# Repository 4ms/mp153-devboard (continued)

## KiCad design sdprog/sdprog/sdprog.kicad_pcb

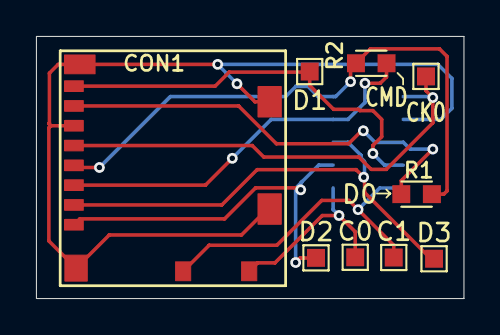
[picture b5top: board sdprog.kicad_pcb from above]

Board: 2 copper layers, 23.7 x 14.6 mm, 10 parts (1 on the bottom side), 10 nets.

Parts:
C0, C1: TestPoint; TestPoint_Pad_1.0x1.0mm
CK0: TestPoint; TestPoint_Pad_1.0x1.0mm
CON1: microSDCon_SMT_104031-0811; CardSlot_MicroSD_Molex_104031-0811
D1, D2, D3: TestPoint; TestPoint_Pad_1.0x1.0mm
J1: Socket_02x05_P1.27mm_SMT; Socket_2x05_1.27mm_SMD
R1, R2: 10k_0603; R_0603

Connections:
+3.3V: CON1.4 (VDD), J1.1, R1.1, R2.1
/CD0: C0.1, CON1.10 (SDDET1), J1.9 (GND)
/CD1: C1.1, CON1.11 (SDDET2), J1.10 (GND)
/SDMMC_CLK: CK0.1, CON1.5 (CLK), J1.2
/SDMMC_CMD: CON1.3 (CMD), J1.3, R2.2
/SDMMC_D0: CON1.7 (DAT0), J1.6, R1.2
/SDMMC_D1: CON1.8 (DAT1), D1.1, J1.8 (+12V)
/SDMMC_D2: CON1.1 (DAT2), D2.1, J1.7 (12V)
/SDMMC_D3: CON1.2 (CD/DAT3), D3.1, J1.5 (+12V)
GND: CON1.6 (VSS), CON1.9 (SHELL1), J1.4

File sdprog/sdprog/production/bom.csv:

Designator,Footprint,Quantity,Value,LCSC Part #
"C0, C1, CK0, D1, D2, D3",TestPoint_Pad_1.0x1.0mm,6,TestPoint,
CON1,CardSlot_MicroSD_Molex_104031-0811,1,microSDCon_SMT_104031-0811,C585350
J1,Socket_2x05_1.27mm_SMD,1,Socket_02x05_P1.27mm_SMT,
"R1, R2",R_0603,2,10k_0603,C98220

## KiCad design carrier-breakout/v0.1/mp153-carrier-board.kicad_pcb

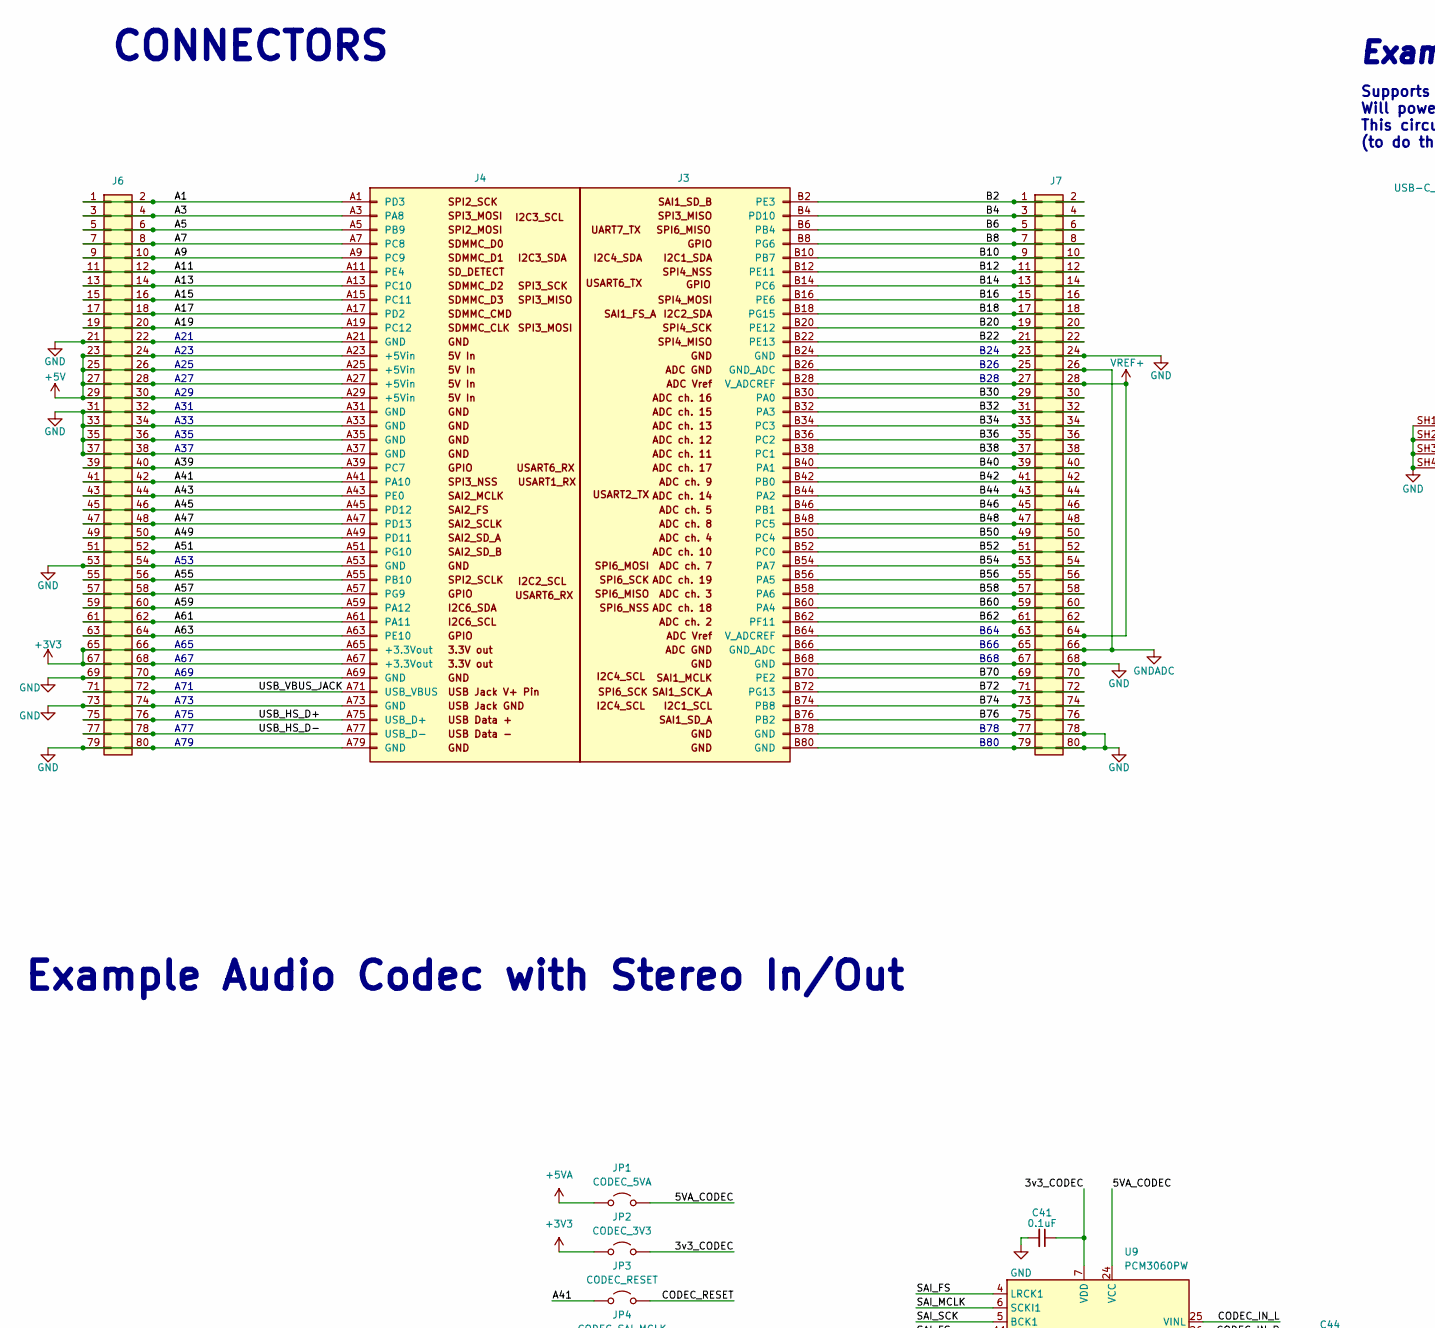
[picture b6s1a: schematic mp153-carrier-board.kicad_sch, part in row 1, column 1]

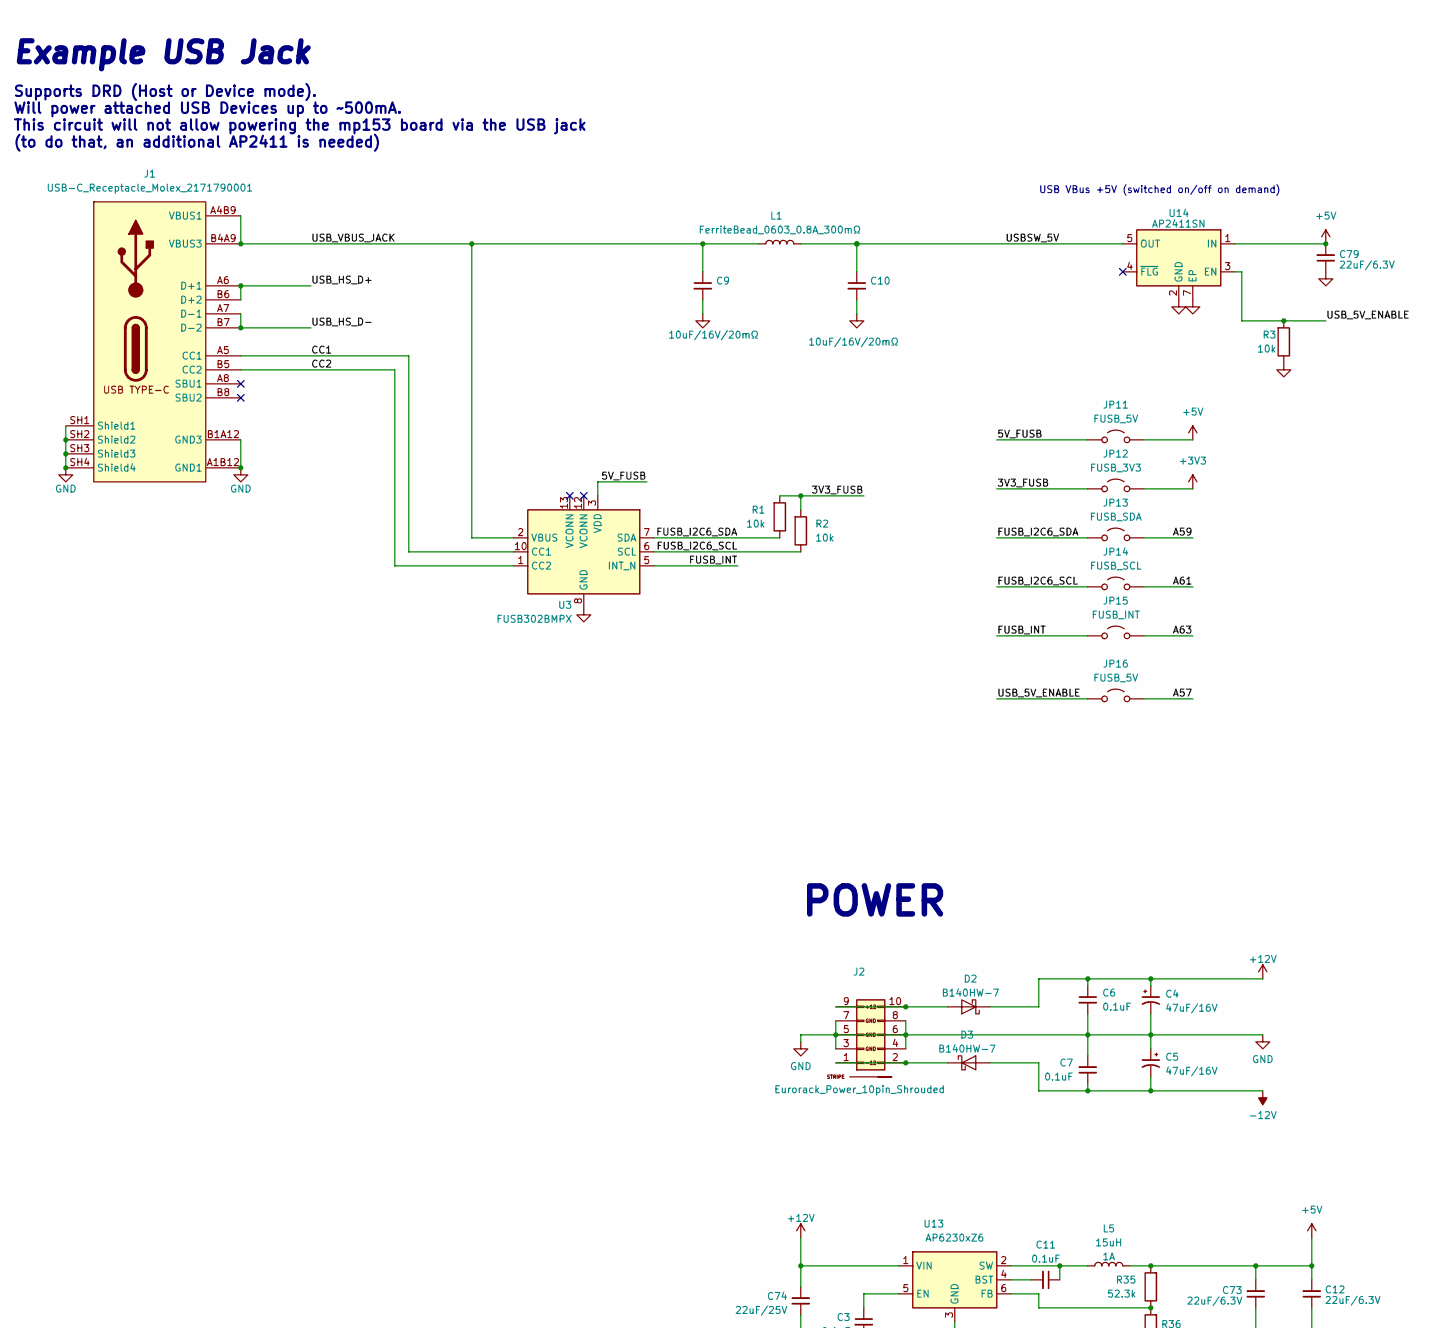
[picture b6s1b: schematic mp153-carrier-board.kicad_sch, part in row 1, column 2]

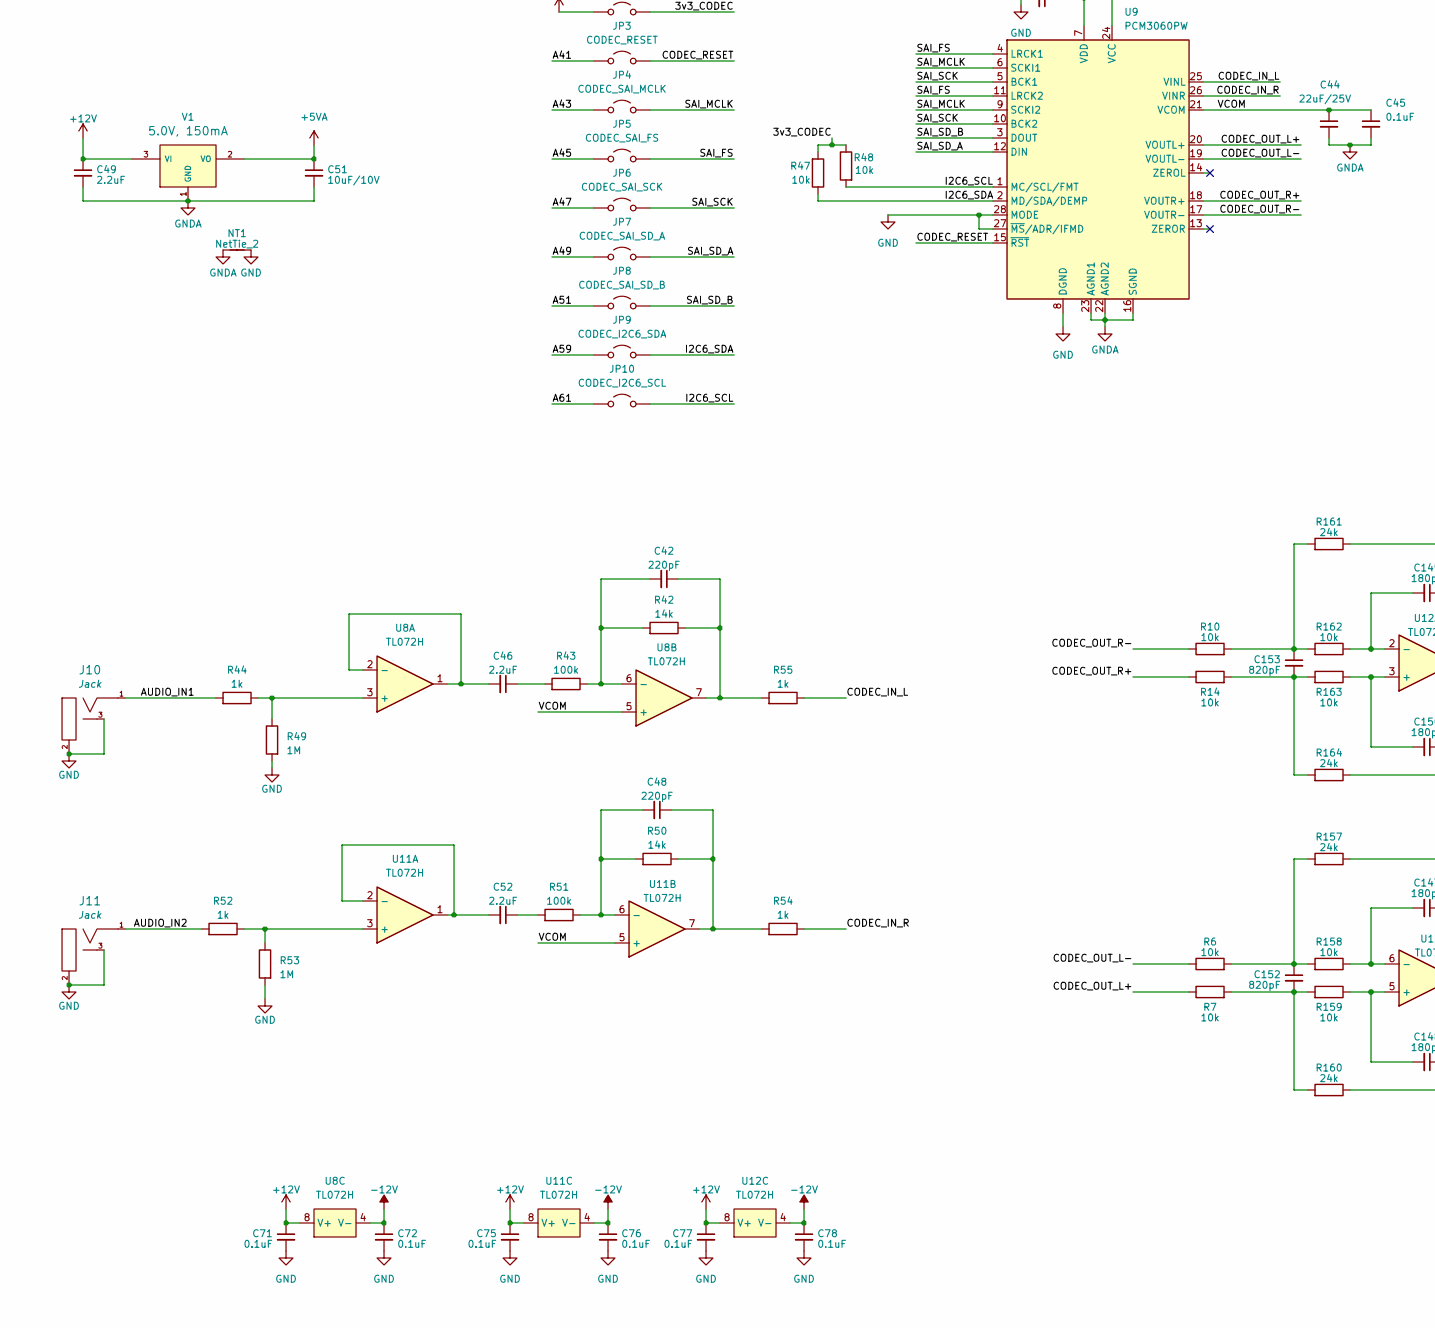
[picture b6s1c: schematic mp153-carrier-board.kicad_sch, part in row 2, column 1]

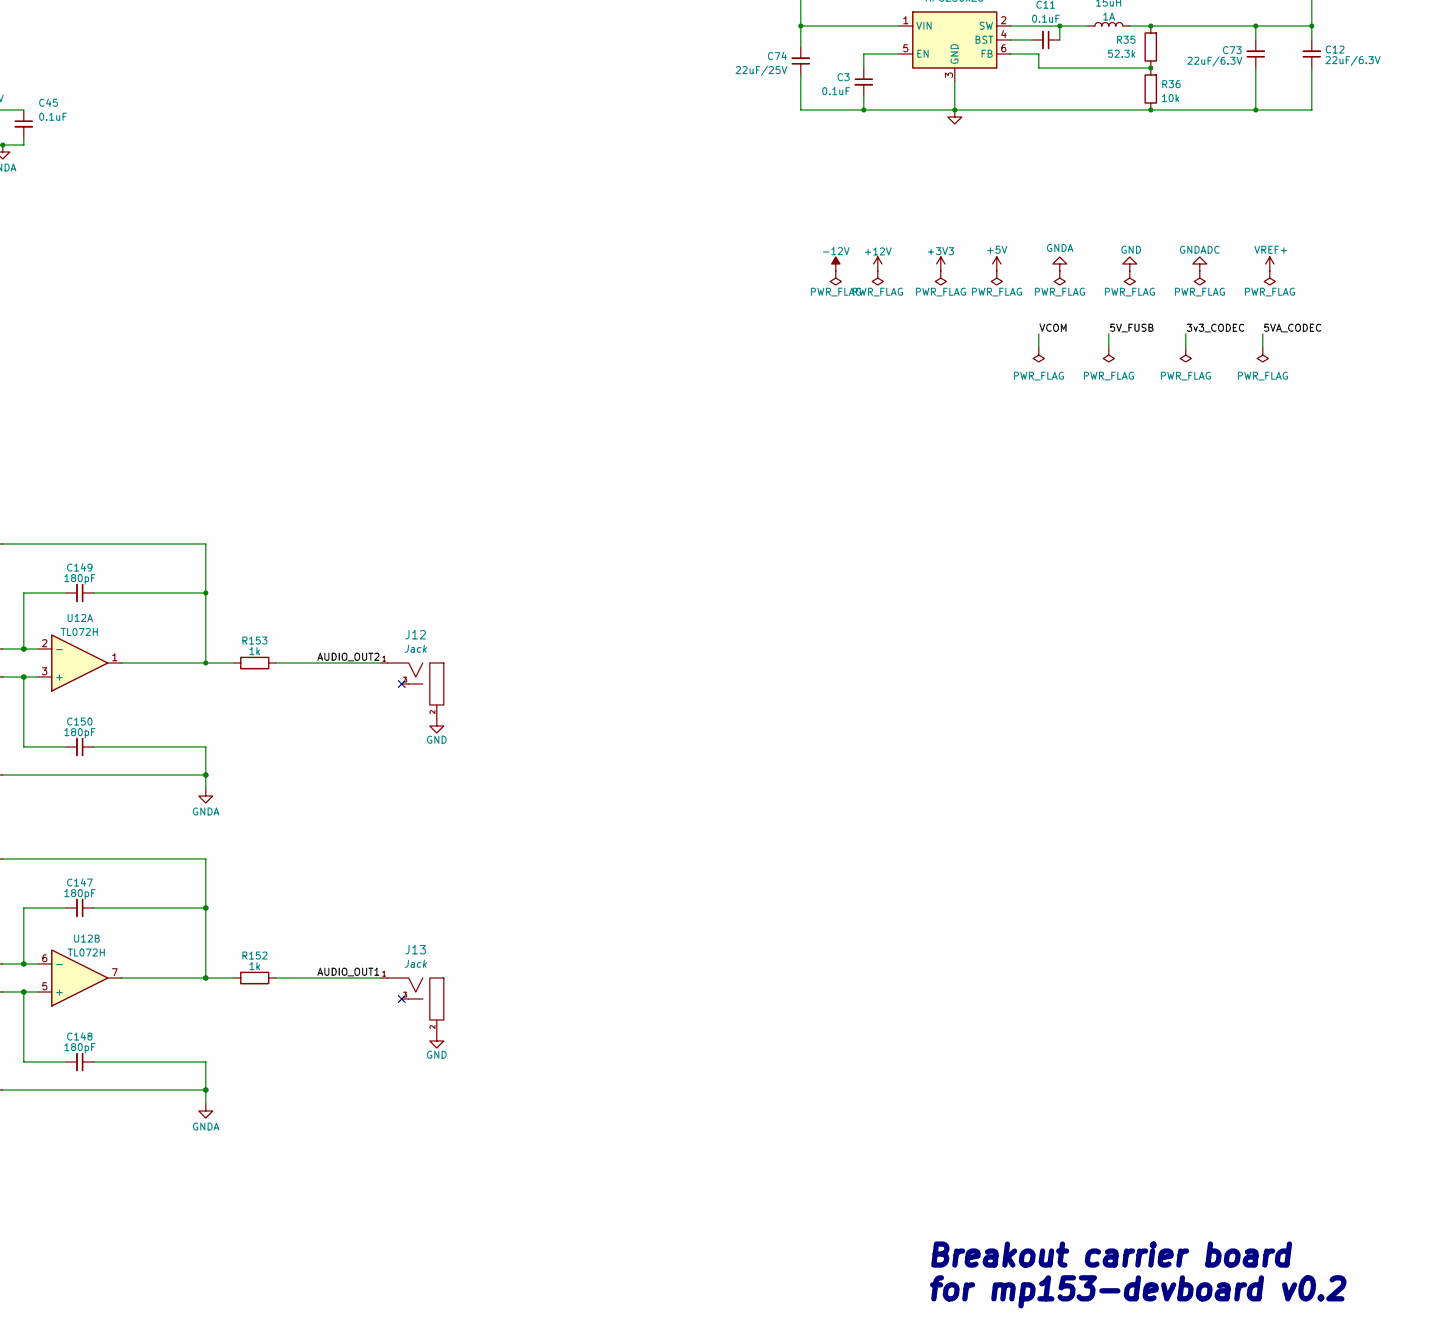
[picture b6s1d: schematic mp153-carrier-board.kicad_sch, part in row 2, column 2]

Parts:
C3, C11, C41, C45: 100nF_0402_50V; C_0402; Part Number GCM155R71C104KA55D; JLCPCB ID C1525
C4, C5: 47uF_5x5.3_16V; CP_Elec_5x5.3; Part Number VES470M1CTR-0505; JLCPCB ID C134798
C6, C7: 100nF_0603_16V; C_0603; Part Number 0603YC104KAT2A; JLCPCB ID C14663
C9, C10: 10uF_0805_16V_lowESR; C_0805; Part Number EMK212ABJ106KG-T; JLCPCB ID C190442
C12, C73, C79: 22uF_0603_6.3V; C_0603; Part Number GRM188R60J226MEA0J; JLCPCB ID C59461
C42, C48: 220pF_0603_25V; C_0603; Part Number CC0603JRNPO9BN221; JLCPCB ID C1603
C44: 22uF_0805_25V; C_0805; Part Number GRM21BR61E226ME44L; JLCPCB ID C45783
C46, C49, C52: 2.2uF_0603_25V; C_0603; Part Number GRM188R6YA225KA12D; JLCPCB ID C57895
C51: 10uF_0603_10V; C_0603; Part Number GRM188R61A106KE69D; JLCPCB ID C19702
C71, C72, C75, C76, C77, C78: 100nF_0402_50V; C_0402; Part Number GRM155R71H104KE14D; JLCPCB ID C307331
C74: 22uF_0805_25V; C_1206; Part Number TMK316BBJ226ML-T; JLCPCB ID C12891
C147, C148, C149, C150: 180pF_0402_25V; C_0402; Part Number GRM1555C2A181JE01D; JLCPCB ID C106999
C152, C153: 820pF_0402_10v; C_0402; Part Number 0402ZC821KAT2A; JLCPCB ID C565563
D2, D3: B140HW-7; D_SOD-123; Part Number B140HW-7; JLCPCB ID C134429
J1: USB-C_Receptacle_Molex_2171790001; USB_C_Receptacle_Molex_2171790001; Part Number 217179-0001; JLCPCB ID C2894899
J2: Eurorack_Power_10pin_Shrouded; Pins_2x05_2.54mm_TH_EurorackPower_Shrouded; Part Number 61201021621
J3: mp153-devboard-sockets_B; Part Number DF40HC(3.0)-80DS-0.4V(51); JLCPCB ID C2858577
J4: mp153-devboard-sockets_A; Part Number DF40HC(3.0)-80DS-0.4V(51); JLCPCB ID C2858577
J6, J7: Pins_02x40_P2.54mm_TH; Pins_2x40_P2.54mm_TH
J10, J11, J12, J13: 3.5mm_Mono_Switched_sm; EighthInch_PJ398SM; Part Number WQP-WQP518MA
JP1, JP2, JP3, JP4, JP5, JP6, JP7, JP8, JP9, JP10, JP11, JP12, JP13, JP14, JP15, JP16: SolderJumper_2_Open; JUMPER_SMD_1x2_tiny
L1: FerriteBead_0603_0.8A_300mΩ; R_0603; Part Number MPZ1608S102ATA00; JLCPCB ID C76814
L5: 15uH_1A_5040; COIL_5040; Part Number SRN5040TA-150M; JLCPCB ID C222950
NT1: NetTie_2; NetTie-2_SMD_Pad0.5mm
R1, R2, R3, R6, R7, R10, R14, R36, R47, R48, R158, R159, R162, R163: 10k_0402; R_0402; Part Number RC0402FR-0710KL; JLCPCB ID C60490
R35: 52.3k_0402; R_0402; Part Number RC0402FR-0752K3L; JLCPCB ID C276275
R42, R50: 14k_0402; R_0402; Part Number RC0402FR-0714KL; JLCPCB ID C327372
R43, R51: 100k_0402; R_0402; Part Number RC0402FR-07100KL; JLCPCB ID C60491
R44, R52, R54, R55, R152, R153: 1k_0402; R_0402; Part Number RC0402FR-071KL; JLCPCB ID C106235
R49, R53: 1M_0402; R_0402; Part Number RC0402FR-071ML; JLCPCB ID C138033
R157, R160, R161, R164: 24k_0402; R_0402; Part Number RC0402FR-0724KL; JLCPCB ID C138026
U3: FUSB302BMPX; WQFN-14-1EP_2.5x2.5mm_P0.5mm_EP1.45x1.45mm; Part Number FUSB302BMPX; JLCPCB ID C132291
U8, U11, U12: TL072H; TSSOP-8_4.4x3mm_Pitch0.65mm; Part Number TL072HIPWR; JLCPCB ID C4370341
U9: PCM3060PW; TSSOP-28_4.4x9.7mm_P0.65mm; Part Number PCM3060PW; JLCPCB ID C2651841
U13: AP6230xZ6; SOT-563; Part Number AP62301Z6; JLCPCB ID C1880992
U14: AP2411SN; DFN-6-1EP_2x2mm_P0.65mm_EP1x1.6mm; Part Number AP2411SN-7; JLCPCB ID C2149815
V1: AP2120N-5.0TRG1; SOT23-3_PO132; Part Number AP2120N-5.0TRG1; JLCPCB ID C50754

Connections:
+3V3: J4.A65 (+3.3Vout), J4.A67 (+3.3Vout), J6.65, J6.66, J6.67, J6.68, JP2.1 (A), JP12.2 (B)
+5V: C12.2, C73.2, C79.2, J4.A23 (+5Vin), J4.A25 (+5Vin), J4.A27 (+5Vin), J4.A29 (+5Vin), J6.23, J6.24, J6.25, J6.26, J6.27, J6.28, J6.29, J6.30, JP11.2 (B), L5.2, R35.2, U14.1 (IN)
+5VA: C51.1, JP1.1 (A), V1.2 (VO)
+12V: C4.1, C6.1, C49.1, C71.1, C74.2, C75.1, C77.1, D2.1 (K), U8.8 (V+), U11.8 (V+), U12.8 (V+), U13.1 (VIN), V1.3 (VI)
-12V: C5.2, C7.1, C72.1, C76.1, C78.1, D3.2 (A), U8.4 (V-), U11.4 (V-), U12.4 (V-)
/3V3_FUSB: JP12.1 (A), R1.2, R2.2
/3v3_CODEC: C41.1, JP2.2 (B), R47.2, R48.1, U9.7 (VDD)
/5VA_CODEC: JP1.2 (B), U9.24 (VCC)
/5V_FUSB: JP11.1 (A), U3.3 (VDD), U3.4 (VDD)
/A1: J4.A1 (PD3), J6.1, J6.2
/A3: J4.A3 (PA8), J6.3, J6.4
/A5: J4.A5 (PB9), J6.5, J6.6
/A7: J4.A7 (PC8), J6.7, J6.8
/A9: J4.A9 (PC9), J6.9, J6.10
/A11: J4.A11 (PE4), J6.11, J6.12
/A13: J4.A13 (PC10), J6.13, J6.14
/A15: J4.A15 (PC11), J6.15, J6.16
/A17: J4.A17 (PD2), J6.17, J6.18
/A19: J4.A19 (PC12), J6.19, J6.20
/A39: J4.A39 (PC7), J6.39, J6.40
/A41: J4.A41 (PA10), J6.41, J6.42, JP3.1 (A)
/A43: J4.A43 (PE0), J6.43, J6.44, JP4.1 (A)
/A45: J4.A45 (PD12), J6.45, J6.46, JP5.1 (A)
/A47: J4.A47 (PD13), J6.47, J6.48, JP6.1 (A)
/A49: J4.A49 (PD11), J6.49, J6.50, JP7.1 (A)
/A51: J4.A51 (PG10), J6.51, J6.52, JP8.1 (A)
/A55: J4.A55 (PB10), J6.55, J6.56
/A57: J4.A57 (PG9), J6.57, J6.58, JP16.2 (B)
/A59: J4.A59 (PA12), J6.59, J6.60, JP9.1 (A), JP13.2 (B)
/A61: J4.A61 (PA11), J6.61, J6.62, JP10.1 (A), JP14.2 (B)
/A63: J4.A63 (PE10), J6.63, J6.64, JP15.2 (B)
/AUDIO_IN1: J10.1 (SIG), R44.2
/AUDIO_IN2: J11.1 (SIG), R52.2
/AUDIO_OUT1: J13.1 (SIG), R152.1
/AUDIO_OUT2: J12.1 (SIG), R153.1
/B2: J3.B2 (PE3), J7.1, J7.2
/B4: J3.B4 (PD10), J7.3, J7.4
/B6: J3.B6 (PB4), J7.5, J7.6
/B8: J3.B8 (PG6), J7.7, J7.8
/B10: J3.B10 (PB7), J7.9, J7.10
/B12: J3.B12 (PE11), J7.11, J7.12
/B14: J3.B14 (PC6), J7.13, J7.14
/B16: J3.B16 (PE6), J7.15, J7.16
/B18: J3.B18 (PG15), J7.17, J7.18
/B20: J3.B20 (PE12), J7.19, J7.20
/B22: J3.B22 (PE13), J7.21, J7.22
/B30: J3.B30 (PA0), J7.29, J7.30
/B32: J3.B32 (PA3), J7.31, J7.32
/B34: J3.B34 (PC3), J7.33, J7.34
/B36: J3.B36 (PC2), J7.35, J7.36
/B38: J3.B38 (PC1), J7.37, J7.38
/B40: J3.B40 (PA1), J7.39, J7.40
/B42: J3.B42 (PB0), J7.41, J7.42
/B44: J3.B44 (PA2), J7.43, J7.44
/B46: J3.B46 (PB1), J7.45, J7.46
/B48: J3.B48 (PC5), J7.47, J7.48
/B50: J3.B50 (PC4), J7.49, J7.50
/B52: J3.B52 (PC0), J7.51, J7.52
/B54: J3.B54 (PA7), J7.53, J7.54
/B56: J3.B56 (PA5), J7.55, J7.56
/B58: J3.B58 (PA6), J7.57, J7.58
/B60: J3.B60 (PA4), J7.59, J7.60
/B62: J3.B62 (PF11), J7.61, J7.62
/B70: J3.B70 (PE2), J7.69, J7.70
/B72: J3.B72 (PG13), J7.71, J7.72
/B74: J3.B74 (PB8), J7.73, J7.74
/B76: J3.B76 (PB2), J7.75, J7.76
/CC1: J1.A5 (CC1), U3.10 (CC1), U3.11 (CC1)
/CC2: J1.B5 (CC2), U3.1 (CC2), U3.14 (CC2)
/CODEC_IN_L: R55.1, U9.25 (VINL)
/CODEC_IN_R: R54.1, U9.26 (VINR)
/CODEC_OUT_L+: R7.1, U9.20 (VOUTL+)
/CODEC_OUT_L-: R6.1, U9.19 (VOUTL-)
/CODEC_OUT_R+: R14.1, U9.18 (VOUTR+)
/CODEC_OUT_R-: R10.1, U9.17 (VOUTR-)
/CODEC_RESET: JP3.2 (B), U9.15 (~RST)
/FUSB_I2C6_SCL: JP14.1 (A), R2.1, U3.6 (SCL)
/FUSB_I2C6_SDA: JP13.1 (A), R1.1, U3.7 (SDA)
/FUSB_INT: JP15.1 (A), U3.5 (INT_N)
/I2C6_SCL: JP10.2 (B), R48.2, U9.1 (MC/SCL/FMT)
/I2C6_SDA: JP9.2 (B), R47.1, U9.2 (MD/SDA/DEMP)
/SAI_FS: JP5.2 (B), U9.4 (LRCK1), U9.11 (LRCK2)
/SAI_MCLK: JP4.2 (B), U9.6 (SCKI1), U9.9 (SCKI2)
/SAI_SCK: JP6.2 (B), U9.5 (BCK1), U9.10 (BCK2)
/SAI_SD_A: JP7.2 (B), U9.12 (DIN)
/SAI_SD_B: JP8.2 (B), U9.3 (DOUT)
/USBSW_5V: C10.1, L1.1, U14.5 (OUT)
/USB_5V_ENABLE: JP16.1 (A), R3.2, U14.3 (EN)
/USB_HS_D+: J1.A6 (D+1), J1.B6 (D+2), J4.A75 (USB_D+), J6.75, J6.76
/USB_HS_D-: J1.A7 (D-1), J1.B7 (D-2), J4.A77 (USB_D-), J6.77, J6.78
/USB_VBUS_JACK: C9.1, J1.A4B9 (VBUS1), J1.B4A9 (VBUS3), J4.A71 (USB_VBUS), J6.71, J6.72, L1.2, U3.2 (VBUS)
/VCOM: C44.1, C45.1, U8.5 (+), U9.21 (VCOM), U11.5 (+)
GND: C3.2, C4.2, C5.1, C6.2, C7.2, C9.2, C10.2, C12.1, C41.2, C71.2, C72.2, C73.1, C74.1, C75.2, C76.2, C77.2, C78.2, C79.1, J1.A1B12 (GND1), J1.B1A12 (GND3), J1.SH1 (Shield1), J1.SH2 (Shield2), J1.SH3 (Shield3), J1.SH4 (Shield4), J2.3 (GND), J2.4 (GND), J2.5 (GND), J2.6 (GND), J2.7 (GND), J2.8 (GND), J3.B24 (GND), J3.B68 (GND), J3.B78 (GND), J3.B80 (GND), J4.A21 (GND), J4.A31 (GND), J4.A33 (GND), J4.A35 (GND), J4.A37 (GND), J4.A53 (GND), J4.A69 (GND), J4.A73 (GND), J4.A79 (GND), J6.21, J6.22, J6.31, J6.32, J6.33, J6.34, J6.35, J6.36, J6.37, J6.38, J6.53, J6.54, J6.69, J6.70, J6.73, J6.74, J6.79, J6.80, J7.23, J7.24, J7.67, J7.68, J7.77, J7.78, J7.79, J7.80, J10.2 (SHEILD), J10.3 (SW), J11.2 (SHEILD), J11.3 (SW), J12.2 (SHEILD), J13.2 (SHEILD), NT1.2, R3.1, R36.1, R49.2, R53.2, U3.8 (GND), U3.9 (GND), U3.15 (GND), U9.8 (DGND), U9.27 (~MS/ADR/IFMD), U9.28 (MODE), U13.3 (GND), U14.2 (GND), U14.7 (EP)
GNDA: C44.2, C45.2, C49.2, C51.2, C148.1, C150.1, NT1.1, R160.1, R164.1, U9.16 (SGND), U9.22 (AGND2), U9.23 (AGND1), V1.1 (GND)
GNDADC: J3.B26 (GND_ADC), J3.B66 (GND_ADC), J7.25, J7.26, J7.65, J7.66
unnamed: C42.1, R42.1, R55.2, U8.7
unnamed: C46.1, R43.2
unnamed: C48.1, R50.1, R54.2, U11.7
unnamed: C52.1, R51.2
unnamed: C147.1, R152.2, R157.1, U12.7
unnamed: C149.1, R153.2, R161.1, U12.1
unnamed: C152.1, R6.2, R157.2, R158.2
unnamed: C152.2, R7.2, R159.2, R160.2
unnamed: C153.1, R10.2, R161.2, R162.2
unnamed: C153.2, R14.2, R163.2, R164.2
unnamed: D2.2 (A), J2.9 (+12V), J2.10 (+12V)
unnamed: D3.1 (K), J2.1 (-12V), J2.2 (-12V)
unnamed: R44.1, R49.1, U8.3 (+)
unnamed: C46.2, U8.1, U8.2 (-)
unnamed: C42.2, R42.2, R43.1, U8.6 (-)
unnamed: R52.1, R53.1, U11.3 (+)
unnamed: C52.2, U11.1, U11.2 (-)
unnamed: C48.2, R50.2, R51.1, U11.6 (-)
unnamed: C150.2, R163.1, U12.3 (+)
unnamed: C149.2, R162.1, U12.2 (-)
unnamed: C148.2, R159.1, U12.5 (+)
unnamed: C147.2, R158.1, U12.6 (-)
unnamed: C11.2, U13.4 (BST)
unnamed: C3.1, U13.5 (EN)
unnamed: R35.1, R36.2, U13.6 (FB)
unnamed: C11.1, L5.1, U13.2 (SW)
VREF+: J3.B28 (V_ADCREF), J3.B64 (V_ADCREF), J7.27, J7.28, J7.63, J7.64

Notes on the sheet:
A73
A37
A33
A77
POWER
B80
A65
B64
A25
A71
A69
B28
B24
CONNECTORS
B26
B68
Supports DRD (Host or Device mode). Will power attached USB Devices up to ~500mA. This circuit will not allow powering the mp153 board via the USB jack (to do that, an additional AP2411 is needed)
A79
A75
Example USB Jack
A67
Example Audio Codec with Stereo In/Out
A31
A29
A21
Breakout carrier board for mp153-devboard v0.2
B78
B66
A35
USB VBus +5V (switched on/off on demand)
A53
A23
A27

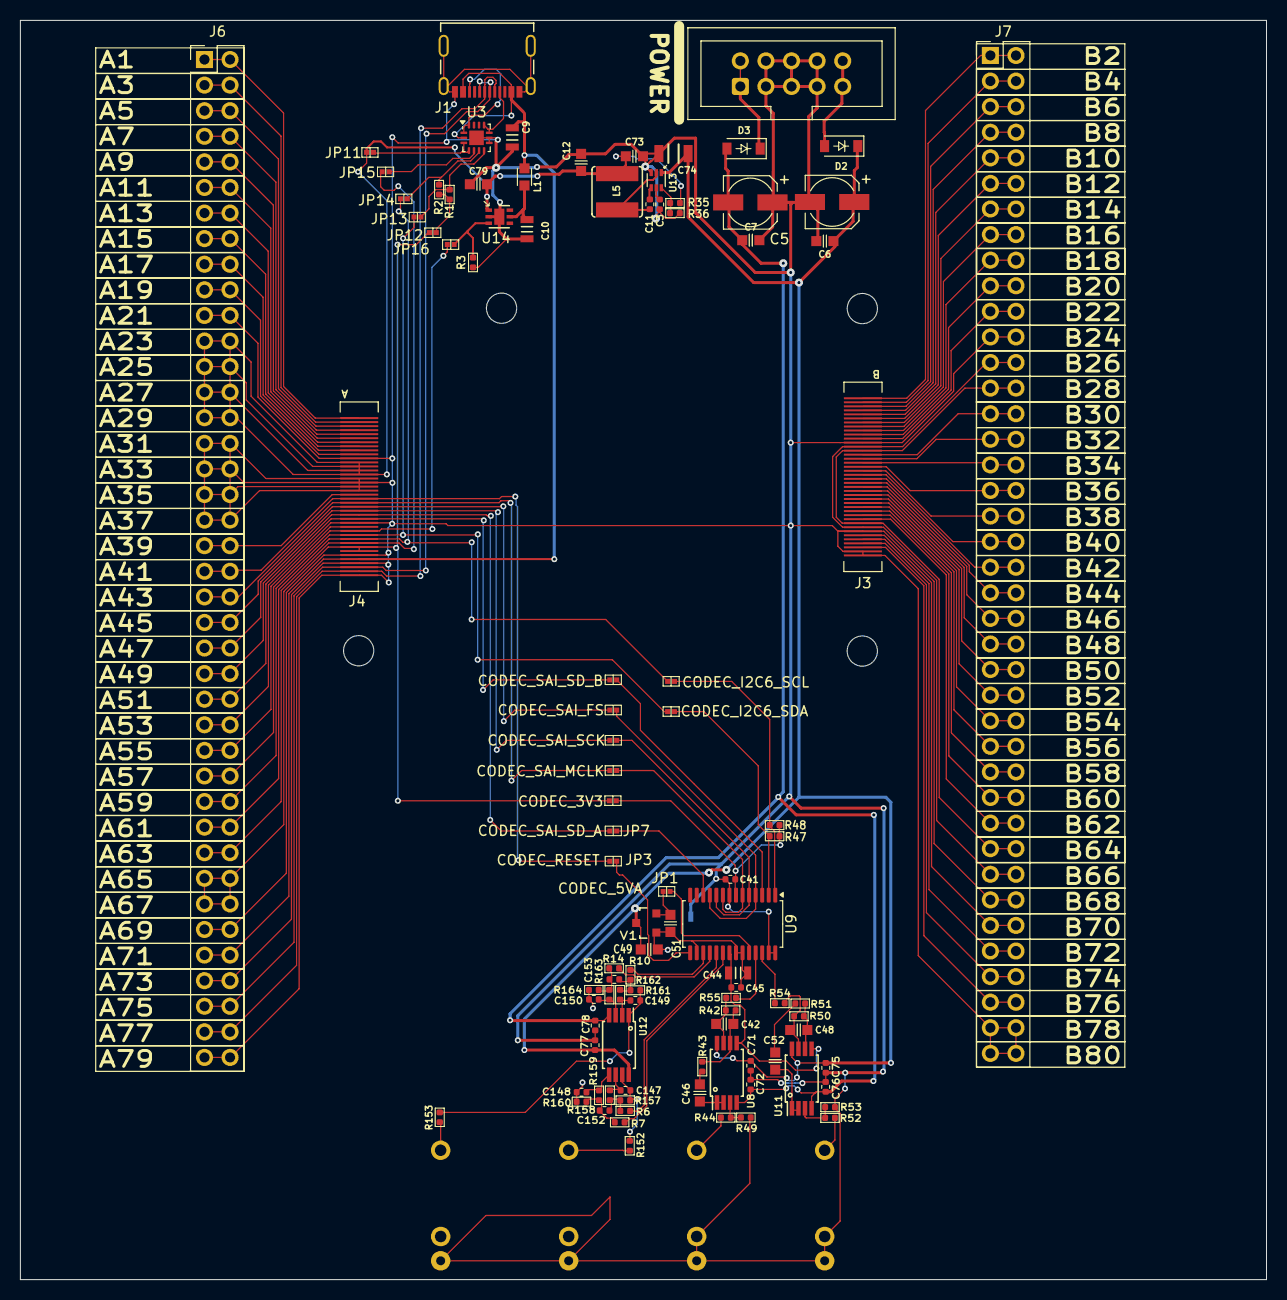
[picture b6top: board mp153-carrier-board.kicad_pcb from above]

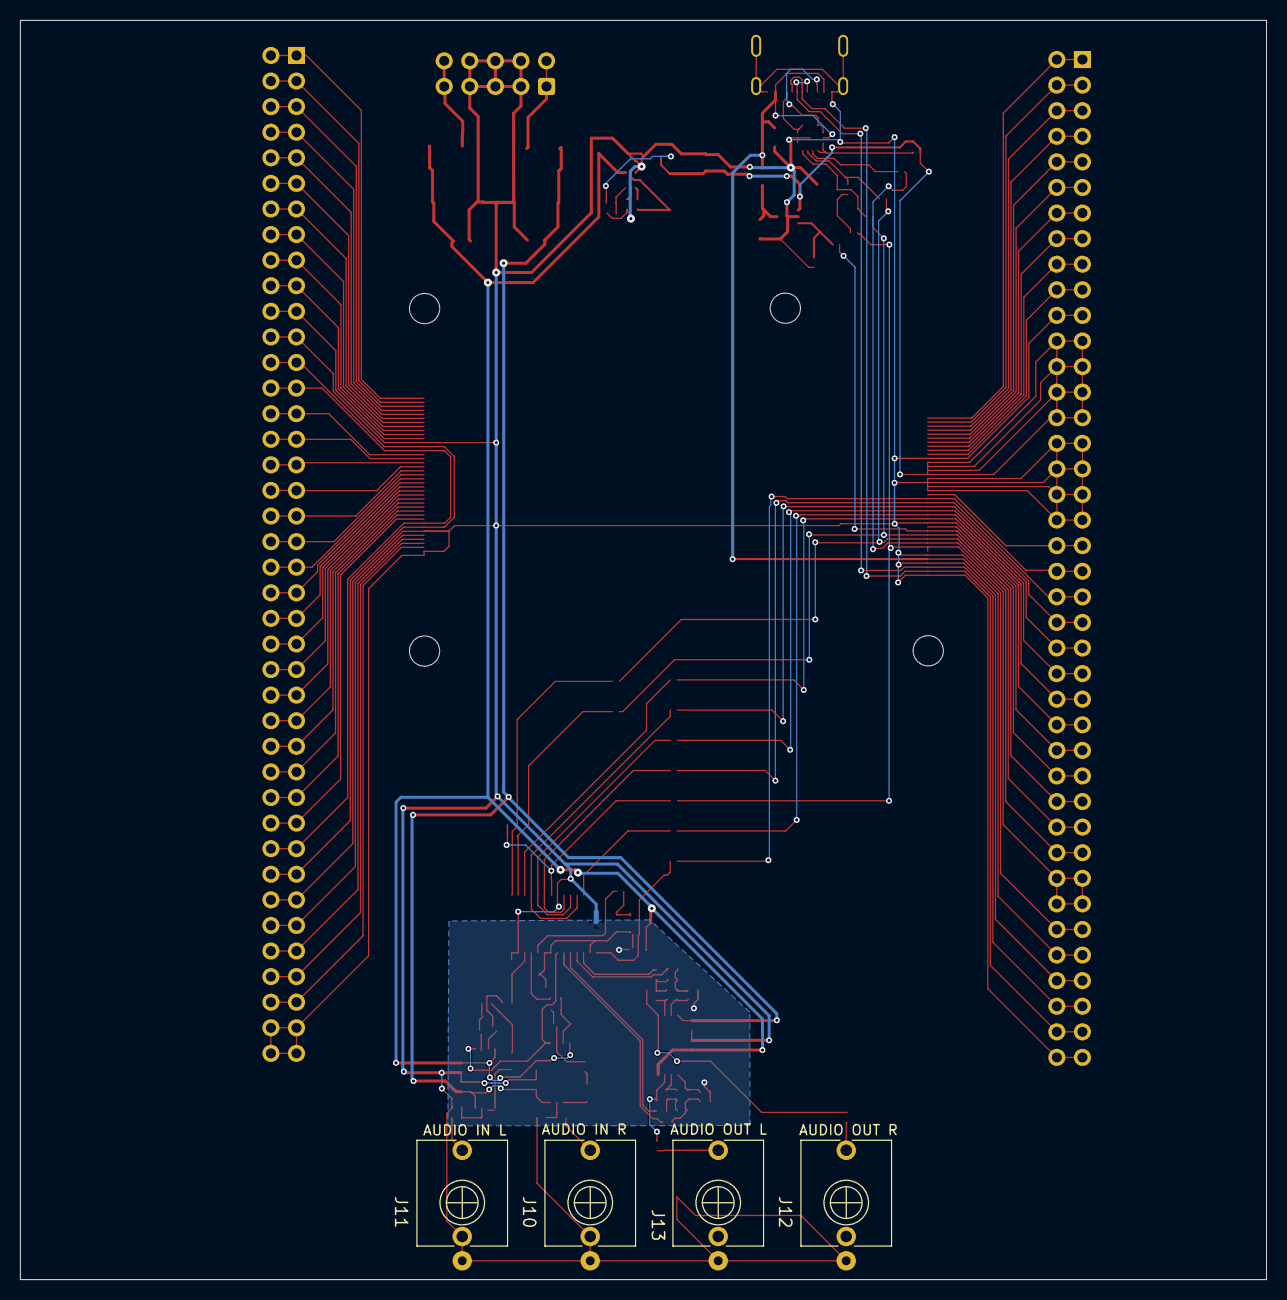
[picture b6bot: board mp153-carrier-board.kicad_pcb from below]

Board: 2 copper layers, 123.7 x 125.0 mm, 103 parts (5 on the bottom side), 122 nets.

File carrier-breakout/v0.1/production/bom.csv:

Designator,Footprint,Quantity,Value,LCSC Part #
"C10, C9",C_0805,2,10uF_0805_16V_lowESR,C190442
"C11, C3, C41, C45",C_0402,4,100nF_0402_50V,C1525
"C12, C73, C79",C_0603,3,22uF_0603_6.3V,C59461
"C147, C148, C149, C150",C_0402,4,180pF_0402_25V,C106999
"C152, C153",C_0402,2,820pF_0402_10v,C565563
"C4, C5",CP_Elec_5x5.3,2,47uF_5x5.3_16V,C134798
"C42, C48",C_0603,2,220pF_0603_25V,C1603
C44,C_0805,1,22uF_0805_25V,C45783
"C46, C49, C52",C_0603,3,2.2uF_0603_25V,C57895
C51,C_0603,1,10uF_0603_10V,C19702
"C6, C7",C_0603,2,100nF_0603_16V,C14663
"C71, C72, C75, C76, C77, C78",C_0402,6,100nF_0402_50V,C307331
C74,C_1206,1,22uF_0805_25V,C12891
"D2, D3",D_SOD-123,2,B140HW-7,C134429
J1,USB_C_Receptacle_Molex_2171790001,1,USB-C_Receptacle_Molex_2171790001,C2894899
"J10, J11, J12, J13",EighthInch_PJ398SM,4,3.5mm_Mono_Switched_sm,
J2,Pins_2x05_2.54mm_TH_EurorackPower_Shrouded,1,Eurorack_Power_10pin_Shrouded,
J3,mp153-devboard-sockets_B,1,~,C2858577
J4,mp153-devboard-sockets_A,1,~,C2858577
"J6, J7",Pins_2x40_P2.54mm_TH,2,Pins_02x40_P2.54mm_TH,
"JP1, JP10, JP11, JP12, JP13, JP14, JP15, JP16, JP2, JP3, JP4, JP5, JP6, JP7, JP8, JP9",JUMPER_SMD_1x2_tiny,16,SolderJumper_2_Open,
L1,R_0603,1,FerriteBead_0603_0.8A_300mΩ,C76814
L5,COIL_5040,1,15uH_1A_5040,C222950
"R1, R10, R14, R158, R159, R162, R163, R2, R3, R36, R47, R48, R6, R7",R_0402,14,10k_0402,C60490
"R152, R153, R44, R52, R54, R55",R_0402,6,1k_0402,C106235
"R157, R160, R161, R164",R_0402,4,24k_0402,C138026
R35,R_0402,1,52.3k_0402,C276275
"R42, R50",R_0402,2,14k_0402,C327372
"R43, R51",R_0402,2,100k_0402,C60491
"R49, R53",R_0402,2,1M_0402,C138033
"U11, U12, U8",TSSOP-8_4.4x3mm_Pitch0.65mm,3,TL072H,C4370341
U13,SOT-563,1,AP6230xZ6,C1880992
U14,DFN-6-1EP_2x2mm_P0.65mm_EP1x1.6mm,1,AP2411SN,C2149815
U3,WQFN-14-1EP_2.5x2.5mm_P0.5mm_EP1.45x1.45mm,1,FUSB302BMPX,C132291
U9,TSSOP-28_4.4x9.7mm_P0.65mm,1,PCM3060PW,C2651841
V1,SOT23-3_PO132,1,AP2120N-5.0TRG1,C50754

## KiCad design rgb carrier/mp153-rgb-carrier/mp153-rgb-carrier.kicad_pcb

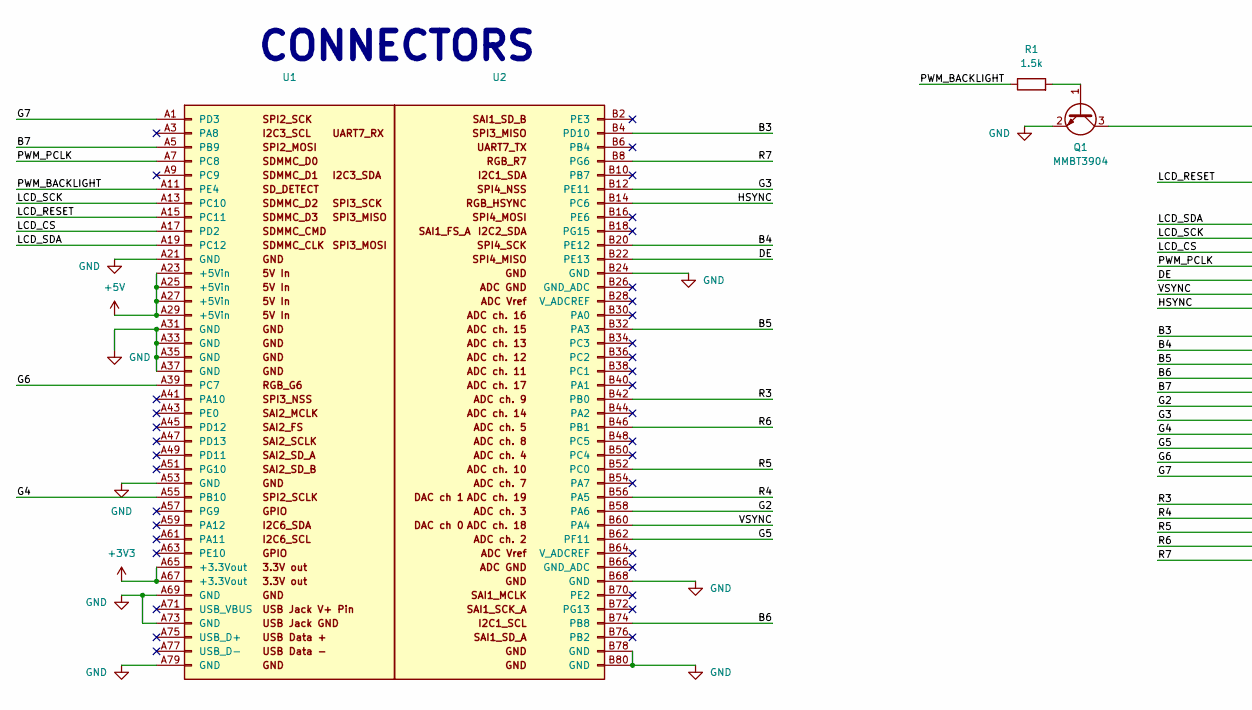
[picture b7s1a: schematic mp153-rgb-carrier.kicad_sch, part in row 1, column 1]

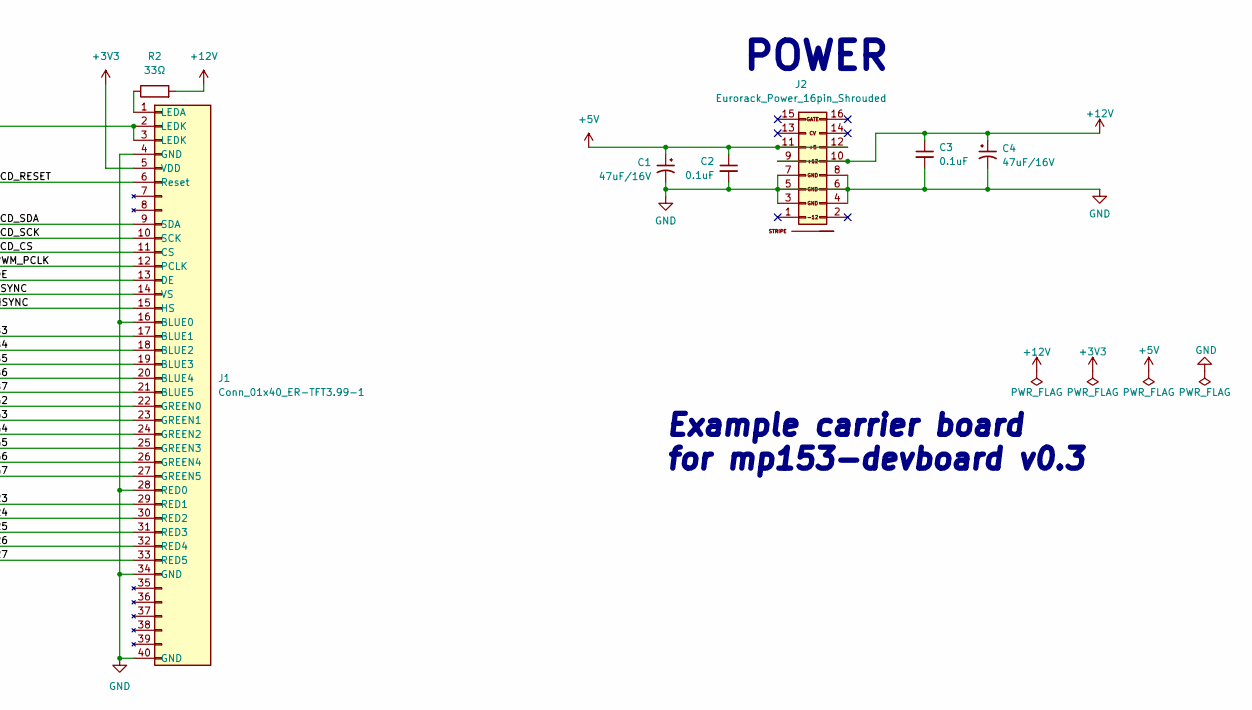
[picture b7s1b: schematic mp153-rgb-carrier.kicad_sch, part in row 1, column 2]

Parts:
C1, C4: 47uF_5x5.3_16V; CP_Elec_5x5.3; Part Number VES470M1CTR-0505; JLCPCB ID C134798
C2, C3: 100nF_0603_16V; C_0603; Part Number 0603YC104KAT2A; JLCPCB ID C14663
J1: Conn_01x40_ER-TFT3.99-1; Amphenol_F32R-1A7x1-11040_1x40-1MP_P0.5mm_Horizontal; Part Number ER-TFT3.99-1
J2: Eurorack_Power_16pin_Shrouded; Pins_2x08_2.54mm_TH_EurorackPower_Shrouded; Part Number LL1007-1 (2*8 HITEMP)
Q1: MMBT3904; TO-92; Part Number MMBT3904-TP; JLCPCB ID C20526
R1: 1.5k_0603; R_Axial_DIN0207_L6.3mm_D2.5mm_P7.62mm_Horizontal; Part Number RC0603FR-071K5L; JLCPCB ID C114668
R2: 33Ω_0603; R_Axial_DIN0207_L6.3mm_D2.5mm_P7.62mm_Horizontal; Part Number RC0603FR-0733RL; JLCPCB ID C108661
U1: mp153-devboard-v0.1-sockets_A
U2: mp153-devboard-v0.1-sockets_B

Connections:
+3V3: J1.5 (VDD), U1.A65 (+3.3Vout), U1.A67 (+3.3Vout)
+5V: C1.1, C2.1, J2.11 (5V), J2.12 (5V), U1.A23 (+5Vin), U1.A25 (+5Vin), U1.A27 (+5Vin), U1.A29 (+5Vin)
+12V: C3.1, C4.1, J2.9 (+12V), J2.10 (+12V), R2.2
/B3: J1.17 (BLUE1), U2.B4 (PD10)
/B4: J1.18 (BLUE2), U2.B20 (PE12)
/B5: J1.19 (BLUE3), U2.B32 (PA3)
/B6: J1.20 (BLUE4), U2.B74 (PB8)
/B7: J1.21 (BLUE5), U1.A5 (PB9)
/DE: J1.13 (DE), U2.B22 (PE13)
/G2: J1.22 (GREEN0), U2.B58 (PA6)
/G3: J1.23 (GREEN1), U2.B12 (PE11)
/G4: J1.24 (GREEN2), U1.A55 (PB10)
/G5: J1.25 (GREEN3), U2.B62 (PF11)
/G6: J1.26 (GREEN4), U1.A39 (PC7)
/G7: J1.27 (GREEN5), U1.A1 (PD3)
/HSYNC: J1.15 (HS), U2.B14 (PC6)
/LCD_CS: J1.11 (CS), U1.A17 (PD2)
/LCD_RESET: J1.6 (Reset), U1.A15 (PC11)
/LCD_SCK: J1.10 (SCK), U1.A13 (PC10)
/LCD_SDA: J1.9 (SDA), U1.A19 (PC12)
/PWM_BACKLIGHT: R1.1, U1.A11 (PE4)
/PWM_PCLK: J1.12 (PCLK), U1.A7 (PC8)
/R3: J1.29 (RED1), U2.B42 (PB0)
/R4: J1.30 (RED2), U2.B56 (PA5)
/R5: J1.31 (RED3), U2.B52 (PC0)
/R6: J1.32 (RED4), U2.B46 (PB1)
/R7: J1.33 (RED5), U2.B8 (PG6)
/VSYNC: J1.14 (VS), U2.B60 (PA4)
GND: C1.2, C2.2, C3.2, C4.2, J1.4 (GND), J1.16 (BLUE0), J1.28 (RED0), J1.34 (GND), J1.40 (GND), J2.3 (GND), J2.4 (GND), J2.5 (GND), J2.6 (GND), J2.7 (GND), J2.8 (GND), Q1.2 (E), U1.A21 (GND), U1.A31 (GND), U1.A33 (GND), U1.A35 (GND), U1.A37 (GND), U1.A53 (GND), U1.A69 (GND), U1.A73 (GND), U1.A79 (GND), U2.B24 (GND), U2.B68 (GND), U2.B78 (GND), U2.B80 (GND)
unnamed: J1.1 (LEDA), R2.1
unnamed: Q1.1 (B), R1.2
unnamed: J1.2 (LEDK), J1.3 (LEDK), Q1.3 (C)

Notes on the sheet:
POWER
CONNECTORS
Example carrier board for mp153-devboard v0.3
